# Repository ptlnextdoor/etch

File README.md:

# Etch

**Claude Code for circuit boards.** Say the board you want. A team of agents picks real KiCad parts, places and routes the board, checks it, and hands you a board you can send to a fab, in 3D.

**Live:** https://etch.chat

## What you can do

<table>
<tr>
<td width="50%"><b>Build anything</b><br>One sentence in, a routed and checked KiCad board out. KiCad's own renders of the board as it's assembled:<br></td>
<td width="50%"><b>See it in 3D</b><br>Every part is its real 3D model. Orbit, zoom, flip it over.<br></td>
</tr>
<tr>
<td><b>Ask about any part</b><br>Click a part and ask what it does. Answers are pinned to the part.<br></td>
<td><b>Restyle it</b><br>Solder mask, silkscreen and finish change live.<br></td>
</tr>
<tr>
<td><b>Start from an open-source board</b><br>Pick any board from the library and change it.<br></td>
<td><b>Export real files</b><br>KiCad project, Gerbers, drill and BOM, checked again on export. Or the 3D model as GLB.<br></td>
</tr>
<tr>
<td><b>See it flat, and as a schematic</b><br>The same board as KiCad plots it (copper, pads, silk, top or bottom) and the schematic Etch drew, with every part and net clickable across the 3D, 2D and schematic views.</td>
<td><b>Make it</b><br>The board's numbers, every check it passed, a rough bare-board estimate, and the fab files (Gerbers, drill, BOM, KiCad project) in one sheet. Before a build, Etch asks one to three quick questions with its own pick marked.</td>
</tr>
<tr>
<td colspan="2"><b>Explore 135 open-source boards</b><br>Real KiCad projects from GitHub, prerendered with every original 3D part model, each credited to its author and licence. Your own builds land in My boards.<br></td>
</tr>
</table>

## How it works

This is the "How Etch works" diagram from the **?** button in the app, playing its two tours: a request travelling from you to a checked 3D board, and a library board being built.

1. **You ask**, by voice or text. Speech-to-text runs locally (Parakeet).
2. **The agent team works it out.** A picker chooses parts, values and wiring, a part scout finds anything missing, and the lead tracks progress and decides when it's done.
3. **The KiCad 10 engine builds it.** Placement and routing, then the fab files and the 3D model.
4. **The agents check their own work.** Every try runs ERC, DRC, schematic-to-PCB parity, unconnected nets, routing, 3D models, an ngspice simulation and the benchmarks the agents wrote for the request. A failure goes back to the picker as a repair, up to three tries, then Etch stops and says why.
5. **You get the board** in 3D, ready to question, restyle, change or export.

### Built on

| | How Etch uses it |
| --- | --- |
| **Crusoe Managed Inference** | The default endpoint for every agent call (`api.inference.crusoecloud.com/v1`), paced to 28 requests a minute across all agents, with OpenAI as a fallback. |
| **NVIDIA Nemotron** | Nemotron 3 Super 120B picks parts and repairs failed designs; Nemotron 3.5 Lightning 30B scouts parts. Thinking is turned off for speed. |
| **You.com** | Searches for parts that aren't in the KiCad library, so the scout can turn them into real KiCad parts. |

## Run it

Needs a Mac on Apple silicon with [Homebrew](https://brew.sh), a Crusoe API key (`CRUSOE_API_KEY`, or the Keychain entry `crusoe-api-key`) and an OpenAI API key for the fallback and spoken replies. A You.com key (`YOU_API_KEY`) turns on web part search.

```bash
git clone https://github.com/PranavAchar01/etch.git
cd etch
./setup.sh
./run.sh
```

`setup.sh` installs uv, ngspice, node, cloudflared and KiCad 10 if they're missing, builds the engine's Python env and downloads the local speech-to-text model (about 500 MB). It asks once for your OpenAI key and an access code of your choice, and stores both in the macOS Keychain.

`run.sh` starts speech-to-text, the backend and the page, then opens http://127.0.0.1:8766. Enter the access code you chose. `./run.sh --public` also opens a Cloudflare tunnel and redeploys the Vercel project linked in `deploy/etch-app` so the public page points at it.

## Layout

| Path | What |
| --- | --- |
| `deploy/etch-app/` | The static site Vercel serves: the Explore library and homepage (`explore.html`, `/` rewrites to it), the board editor (`board.html`, `board.html?new=1` builds a new board from a description) and the UI kit demo (`kit.html`), with `js/` and `css/`. |
| `docs/media/` | The GIFs in this README, cut from recordings of the live site. |
| `deploy/etch-app/world/` | The prerendered open-source boards Explore shows (GLB, thumbnail, parts, credits per board). Built by `library/`. |
| `deploy/etch_public.py` | The backend API the page calls (port 3439). Routes and build events: [deploy/API.md](deploy/API.md). Board view routes are in `deploy/explore.py`. |
| `library/` | Finds licensed KiCad boards on GitHub and prerenders them into `deploy/etch-app/world/` ([library/README.md](library/README.md)). |
| `deploy/*.sh` | How it runs on the host Mac: launchd restart, Cloudflare tunnel, Vercel redeploy, STT keeper. |
| `agent/` | The lead agent and sub-agents that write and repair board specs ([agent/README.md](agent/README.md)). |
| `engine/` | Spec in, verified KiCad board out ([engine/README.md](engine/README.md)). |
| `engine/parts/` | Part index, KiCad catalog, classifier, pre-rendered part images and parts fetched from LCSC or GitHub (`cache/`). |
| `studio/kicad_frames.py` | Board render frames for the page. |
| `studio/stt/stt_server.cjs` | Local speech-to-text (Parakeet on sherpa-onnx, port 3421). |
| `vendor/espressif-kicad-libraries/` | ESP32 parts from Espressif's KiCad library 3.2.1 (CC-BY-SA 4.0, see its PROVENANCE.md). |

Build outputs (`engine/out/`) and the usage meter (`qa/`) are created at run time and are not in the repo.

## Deploying Explore

`deploy/redeploy.sh` uploads `deploy/etch-app/` as is, including `world/` (about 155 MB). Before running it:

1. Restart the backend so it loads `deploy/explore.py` (`deploy/restart.sh`), and check `/etch/health`.
2. Open `explore.html` and `board.html?id=gh:OLIMEX/ESP32-POE/HARDWARE/ESP32-PoE-hardware-revision-M2` against the local backend (`?api=http://127.0.0.1:3439`). Ask a question, pin a comment on a part and delete it.
3. `world/` holds GPL, CC-BY-SA and CERN-OHL-S boards. Each board page shows its author, repo, commit and licence; keep those visible.

To add or refresh boards: see [library/README.md](library/README.md), then commit `world/` and `library/manifest.json`.

## Settings

Environment variables, all optional:

- `ETCH_MODEL` and `ETCH_SUB_MODEL`: models for the lead agent and the sub-agents (default `nvidia/NVIDIA-Nemotron-3-Super-120B-A12B` and `nvidia/Nemotron-3.5-Lightning-30B-A3B`). `ETCH_BASE_URL` points at any OpenAI-compatible endpoint (default Crusoe Managed Inference). See [agent/config.py](agent/config.py).
- `CRUSOE_API_KEY`, `YOU_API_KEY`: used instead of the Keychain entries when set.
- `OPENAI_API_KEY` and `ETCH_ACCESS_CODE`: used instead of the Keychain entries when set.
- `ETCH_KICAD_APP`, `ETCH_STT_HOME`, `ETCH_HEAVY_LOCK`: written to `.etch.env` by `setup.sh`.

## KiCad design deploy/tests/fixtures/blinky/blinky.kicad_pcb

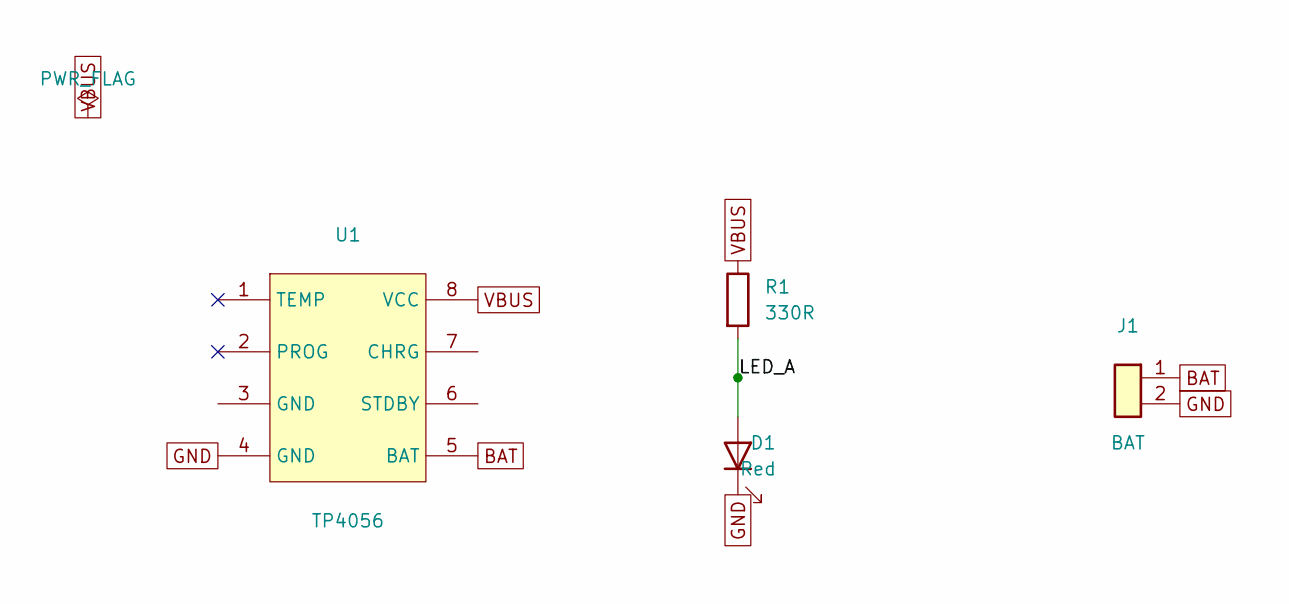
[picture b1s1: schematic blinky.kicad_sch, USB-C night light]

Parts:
D1: Red
J1: BAT
R1: 330R
U1: TP4056; ESOP-8_L4.9-W3.9-P1.27-LS6.0-BL-EP

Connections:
BAT: J1.1, U1.5 (BAT)
GND: D1.1 (K), J1.2, U1.4 (GND), U1.9
LED_A: D1.2 (A), R1.2
VBUS: R1.1, U1.8 (VCC)

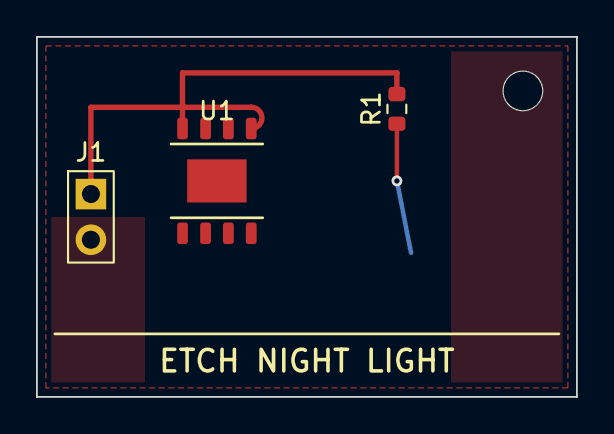
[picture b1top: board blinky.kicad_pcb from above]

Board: 2 copper layers, 30.0 x 20.0 mm, 5 parts (1 on the bottom side), 4 nets.

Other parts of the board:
H1: MountingHole_2.2mm_M2
